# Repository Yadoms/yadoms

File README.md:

<div align="center">

# Yadoms, your home automation solution

**✨ It aims to publish a simple, powerfull, flexible and multiplatforms domotic solution.</a> ✨.**

</div>

<hr>
## Forum

http://www.yadoms.com/forum

## Features

- Edit
- Many devices support
- EnOcean
- ZWave
- RfxCom
- Automation rule
- View customization
- Widgets
- Charts

## Multiplatforms

- Windows
- Linux
- Mac OSX
- Raspberry PI 0,1,2,3,4...
- _probably most of unix based systems_

## Shoutouts

- We thank all the people who contribute, the project exists because of you<br />
- We thank [JetBrains](https://www.jetbrains.com/?from=yadoms) for the licenses<br />

## Licensing

[Refer to LICENSE.md file](LICENSE.md)

## Downloads

[Go to download page](https://github.com/Yadoms/yadoms/releases/)

## Docker

# build the image with the current source code
```bash
docker build -t yadoms .
```

# Run it
```bash
docker run --name yadoms -it -p 8080:8080 yadoms
```

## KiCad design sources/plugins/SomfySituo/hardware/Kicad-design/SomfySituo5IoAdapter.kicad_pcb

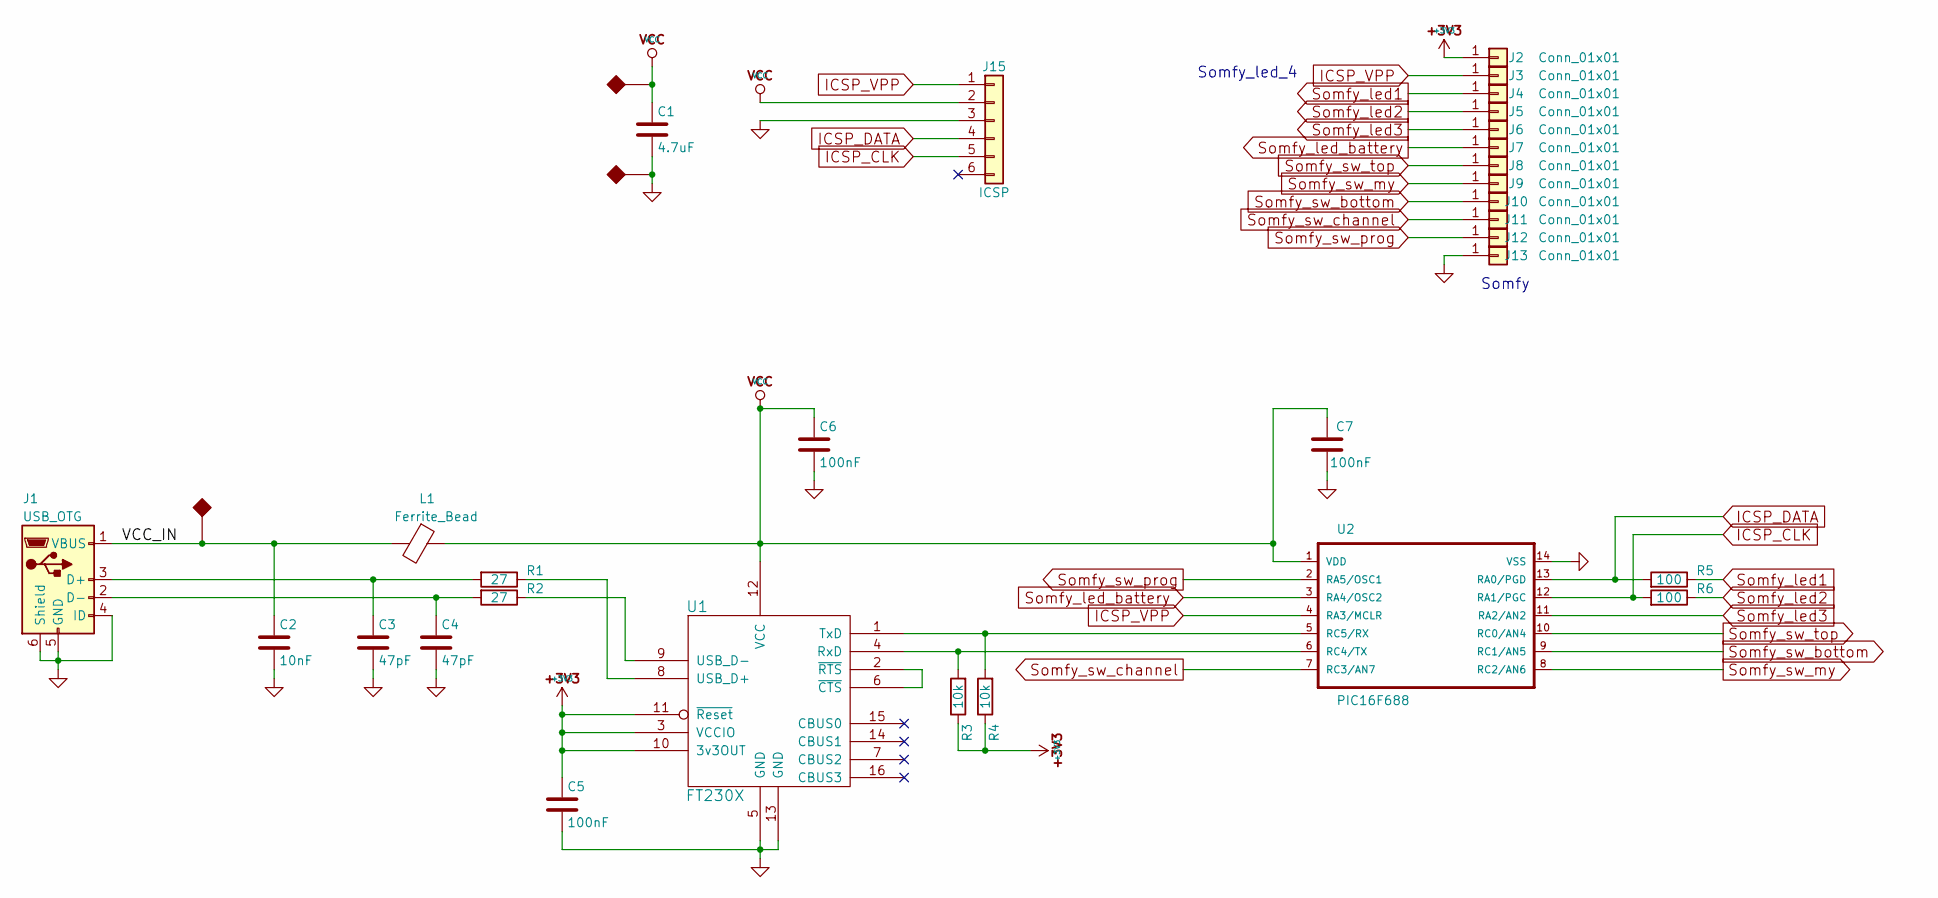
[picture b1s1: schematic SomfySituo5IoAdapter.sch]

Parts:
C1: 4.7uF; C_0805_HandSoldering
C2: 10nF; C_0805_HandSoldering
C3, C4: 47pF; C_0805_HandSoldering
C5, C6, C7: 100nF; C_0805_HandSoldering
J1: USB_OTG; USB_Micro-B_AC0002646
J2, J3, J4, J5, J6, J7, J8, J9, J10, J11, J12, J13: Conn_01x01; Measurement_Point_Square-SMD-Pad_Small
J15: ICSP; AVX_00-9188_006_receiver
L1: Ferrite_Bead; L_0805_HandSoldering
R1, R2: 27; R_0805_HandSoldering
R3, R4: 10k; R_0805_HandSoldering
R5, R6: 100; R_0805_HandSoldering
U1: FT230X; SSOP-16_3.9x4.9mm_Pitch0.635mm
U2: PIC16F688; TSSOP-14_4.4x5mm_Pitch0.65mm

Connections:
+3V3: C5.1, J2.1, R3.1, R4.1, U1.3 (VCCIO), U1.10 (3v3OUT), U1.11 (~Reset)
/VCC_IN: C2.1, J1.1 (VBUS), L1.2
GND: C1.2, C2.2, C3.2, C4.2, C5.2, C6.2, C7.1, J1.4 (ID), J1.5 (GND), J1.6 (Shield), J13.1, J15.3, U1.5 (GND), U1.13 (GND), U2.14 (VSS)
ICSP_CLK: J15.5, R6.2, U2.12 (RA1/PGC)
ICSP_DATA: J15.4, R5.2, U2.13 (RA0/PGD)
ICSP_VPP: J3.1, J15.1, U2.4 (RA3/MCLR)
unnamed: C3.1, J1.3 (D+), R1.2
unnamed: C4.1, J1.2 (D-), R2.2
unnamed: R1.1, U1.8 (USB_D+)
unnamed: R2.1, U1.9 (USB_D-)
unnamed: R3.2, U1.4 (RxD), U2.6 (RC4/TX)
unnamed: R4.2, U1.1 (TxD), U2.5 (RC5/RX)
unnamed: U1.2 (~RTS), U1.6 (~CTS)
Somfy_led1: J4.1, R5.1
Somfy_led2: J5.1, R6.1
Somfy_led3: J6.1, U2.11 (RA2/AN2)
Somfy_led_battery: J7.1, U2.3 (RA4/OSC2)
Somfy_sw_bottom: J10.1, U2.9 (RC1/AN5)
Somfy_sw_channel: J11.1, U2.7 (RC3/AN7)
Somfy_sw_my: J9.1, U2.8 (RC2/AN6)
Somfy_sw_prog: J12.1, U2.2 (RA5/OSC1)
Somfy_sw_top: J8.1, U2.10 (RC0/AN4)
VCC: C1.1, C6.1, C7.2, J15.2, L1.1, U1.12 (VCC), U2.1 (VDD)

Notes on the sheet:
Somfy
Somfy_led_4

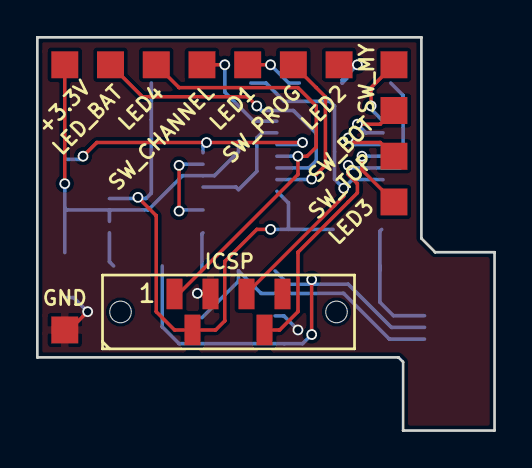
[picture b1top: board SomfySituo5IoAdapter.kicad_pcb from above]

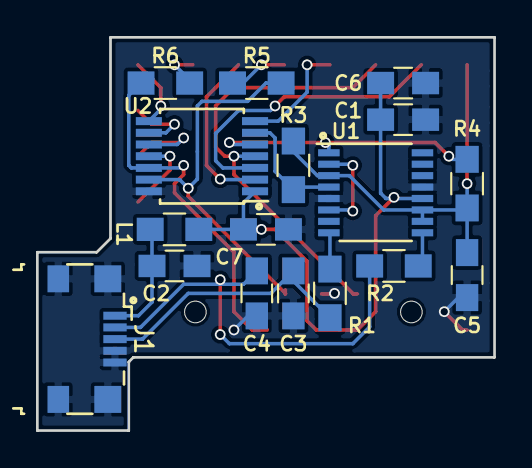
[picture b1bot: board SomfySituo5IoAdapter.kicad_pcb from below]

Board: 2 copper layers, 25.4 x 21.8 mm, 30 parts (17 on the bottom side), 23 nets.

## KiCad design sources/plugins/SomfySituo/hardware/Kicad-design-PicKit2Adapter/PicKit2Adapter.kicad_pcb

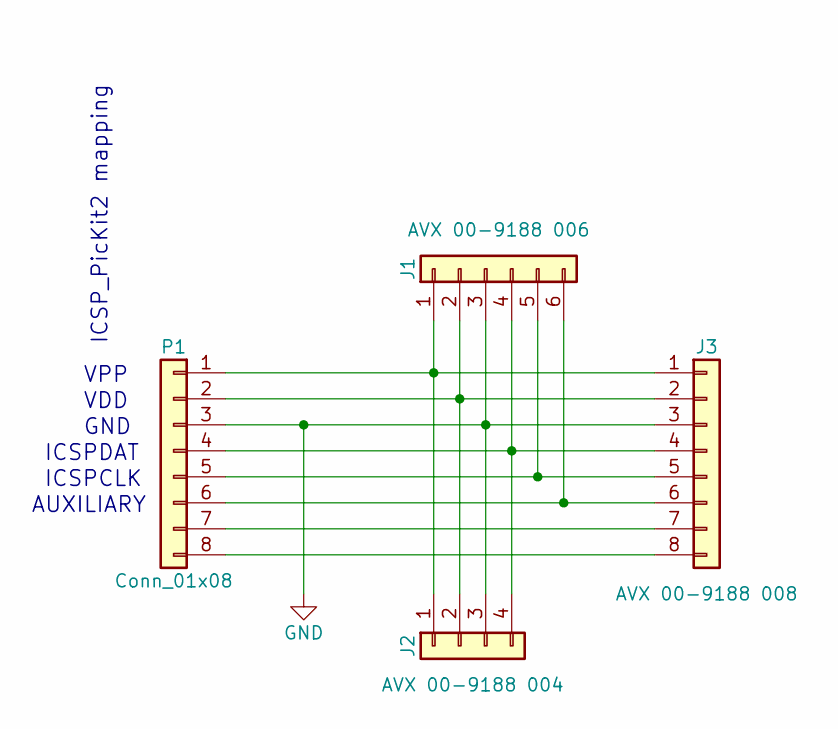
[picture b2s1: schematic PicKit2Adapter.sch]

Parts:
J1: AVX 00-9188 006; AVX_00-9188_006
J2: AVX 00-9188 004; AVX_00-9188_004
J3: AVX 00-9188 008; AVX_00-9188_008
P1: Conn_01x08; Pin_Header_Angled_1x08_Pitch2.54mm

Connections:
GND: J1.3, J2.3, J3.3, P1.3
unnamed: J1.1, J2.1, J3.1, P1.1
unnamed: J1.2, J2.2, J3.2, P1.2
unnamed: J1.4, J2.4, J3.4, P1.4
unnamed: J1.5, J3.5, P1.5
unnamed: J1.6, J3.6, P1.6
unnamed: J3.7, P1.7
unnamed: J3.8, P1.8

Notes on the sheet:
ICSP_PicKit2 mapping
VPP
GND
ICSPDAT
ICSPCLK
AUXILIARY
VDD

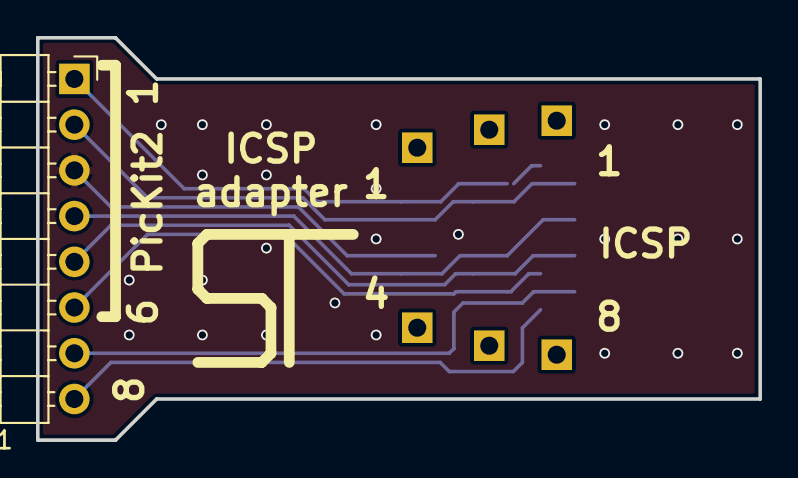
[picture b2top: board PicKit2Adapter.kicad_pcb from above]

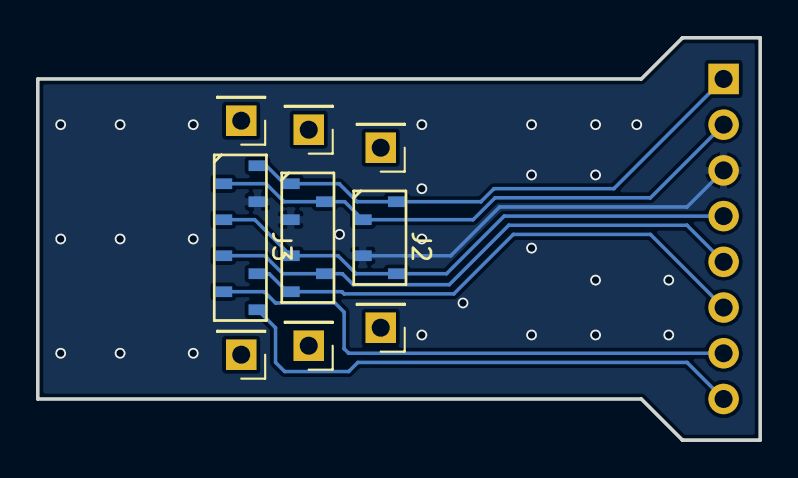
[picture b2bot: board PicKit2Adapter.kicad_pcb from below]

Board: 2 copper layers, 40.1 x 22.4 mm, 4 parts (3 on the bottom side), 8 nets.

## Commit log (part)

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2022-01-07 Refactor updates management
2022-01-10 Fix Yadoms update MD5 check
2022-01-10 Fix Linux build
2022-01-10 Improve 404 management
2022-01-10 Remove TODO
2022-01-10 Add 2 TODOs :-(
2022-01-11 Add updates/forcecheck end-point
2022-01-12 Switch to oatpp v1.3.0 (official release), WIP
2022-01-12 Fix upload
2022-01-13 Manage query params as unordered_multimap
2022-01-13 Add websocket.
    Process IsAlive
2022-01-25 Add new acquisition on websocket management
2022-01-25 Update oatpp
2022-01-25 Revert "Add new acquisition on websocket management"
    This reverts commit 7e2d76df9d03987662bb54e2bf0be462827908ee.
2022-02-03 Manage websocket ping and pong
    Simplify websocket messages format
2022-03-09 Update EnOcean plugin (report some changes from RestApiv2 branch)
2022-03-09 Update build (report some changes from RestApiv2 branch)
2022-03-10 Add D2_04_08 profile support
2022-03-10 Try to fix build
2022-03-10 Add D2_04_XX profiles support
2022-03-11 Update changelog
2022-03-16 Curl v7.82
2022-03-18 Fix curl build
2022-03-28 Add time synchronization message
2022-05-12 Update curlpp options usage
2022-06-05 Update curl (7.83.1)
2022-06-22 Bump Newtonsoft.Json in /ideTools/i18n-check/i18n-check
    Bumps [Newtonsoft.Json](https://github.com/JamesNK/Newtonsoft.Json) from 7.0.1 to 13.0.1.
    - [Release notes](https://github.com/JamesNK/Newtonsoft.Json/releases)
    - [Commits](https://github.com/JamesNK/Newtonsoft.Json/compare/7.0.1...13.0.1)
    ---
    updated-dependencies:
    - dependency-name: Newtonsoft.Json
2022-06-28 Curl 7.84
2022-09-15 Fix websocket closing when shutdown
2022-09-15 Introduce editorconfig file
2022-09-16 Move Poco-specific WS handlers to dedicated folder/namespace
2022-09-16 Add device/keyword creation/deletion WS notifications
2022-09-20 Fix removing unexisting device
2022-09-21 Cleanup (remove CORS handling, only useful for mobile app that would embbed the web client)
2022-09-22 Add GET plugin icon (remove usefulness aliases)
2022-09-22 Add acquisition summary websocket message
2022-09-22 Fix tests
2022-09-23 Add interpreter icon request
2022-09-27 Add HTTPS support
2022-09-27 Speed-up build
2022-09-28 Fix reboot under Linux
2022-09-28 Update changelog
    (cherry picked from commit 9d70c2f2eabac6752474a3c9e9c4166cdc9d2d05)
2022-09-29 Fix can not disable autotest
2022-09-30 Update oatpp-openssl
2022-10-04 Improve MegatecUps (autotest, battery failure detection)
2022-10-05 Disable auto-test if battery declared dead
2022-10-12 Use Curlpp to send emails (Remove Poco)
    Make email subject customizable
2022-10-13 Manage an emails stack in case of connection temporary lost (retry every 2 minutes)
    Supports proxy
2022-10-14 Update MailSender.cpp
    Fix Linux build
2022-10-14 Remove proxy usage (nothing to do with SMTP usage)
2022-10-14 Quick-up cmake
2022-10-17 OATPP is now the default server (on default ports)
2022-10-17 Remove end-point documentation (Swagger)
2022-10-18 Fix mail sender customizable object pattern under Linux
2022-10-19 Add extra-query to reset battery dead flag
2022-10-21 Security patch on configuration
2022-10-21 Use Python3 to run speedtest script
2022-10-21 Update version
2022-10-21 Run speedtest.py script in secure mode
2022-11-15 Enable CORS
2022-11-15 Update /plugins and /plugins-instances parameters and content as camelCase
2022-11-17 Update /system parameters and content as camelCase
2022-11-18 Add pagination in get device REST request (WIP)
2022-11-21 Add pagination on getDevices request
2022-11-28 Update Curlpp
2023-01-03 Fix source file encoding (EnOcean plugin)
2023-01-03 Fix A5-04-xx, A5-09-xx and D2-02-xx devices pairing
2023-01-04 Release EnOcean plugin v2.1.2
2023-02-22 2.5.3
2023-02-26 Add pagination on GET Plugin instances EP
2023-02-26 Add pagination on GET Available Plugin EP
2023-02-28 Fix VS2022 build
2023-02-28 Manage plugins locales (WIP)
2023-03-01 Fix test
2023-03-01 Manage locales (for plugins and interpreters)
2023-03-18 Fix all plugins package.in.json files
2023-03-18 Fix ZWave package.in.json
2023-03-19 Add /system/binding EP
2023-03-22 Filter system plugin for GET /plugins-instances EP
2023-04-03 Populate "__Binding__" fields server-side in available plugins request (WIP)
2023-04-03 Fix containers merge Apply filter to USB devices
2023-04-04 Manage all binding data from plugins
2023-04-04 Manage locale for available plugins request (name, description and configuration schema)
2023-04-05 Fix locales condition
2023-04-05 Fix crash when some plugin has no conf schema
2023-04-05 Improve robustness
2023-04-12 Update SMSDialer descriptions (use markdown for URLs)
2023-04-12 Fix some plugin configurations containing checkbox
2023-04-12 Fix step/precision confusion
2023-04-12 Fix typo
2023-04-14 Use checkboxSection in plugin configurations
2023-04-14 Use time type in configuration
2023-04-15 Add StringExtension::replaceValues
2023-04-16 Use multiselectSection for rfplayer and rfxcom
2023-04-27 Plugin full state
2023-04-29 Fix unit tests
2023-04-29 Fix DataContainer regression
2023-05-15 Manage plugin full states
2023-05-16 Fix unit test
2023-05-16 multiselectSection to multiSelectSection
2023-05-16 Add placeholder and nothingFound in multiselect
2023-05-30 Remove activeSectionText usages.
    Add empty content in Linky package.json
2023-09-20 Add log at REST answer
2023-09-20 Add log on internal server error
2023-09-20 Log exception at available plugin get method
2023-09-20 Remove log
2023-09-20 Fix Linux on OneWire plugin
2023-09-21 add yadoms Dockerfile
2023-09-22 Fix available plugins list build when a plugin is malformed
2023-09-22 Update some dependancies
2023-10-04 SSE (crash at stop)
2023-10-04 Fix SSE crash
2023-10-04 Add connections counter
2023-10-04 Create a SSE connection class (WIP)
2023-10-05 Refactor connection handler
2023-10-06 Send acquisitions in SSE mode
2023-10-11 Handle SSE connection closing
2023-10-12 Finalize SSE POC
2023-10-25 Fix typo in Blockly implementation
2023-11-07 Fix error managment on websocket
2023-11-07 Update dependencies
2023-11-08 Upload logs
2023-11-08 Try to fix cross-compile for Raspberry Pi
2023-11-08 [GH] Generalize upload CMake logs on build failure
2023-11-14 Remove MacOSx support (finally ! :-D )
2023-11-15 Use Oatpp official
2023-12-04 Add type for each item of multiSelectSection
2023-12-05 Fix websocket close
2023-12-05 Log all keywords change
2024-05-31 fix rfxcom package.in.json
2024-05-31 Add Plugin configuration merger (WIP)
2024-05-31 Fix build
2024-06-02 Apply "configurationWithSchema" for CREATE and UPDATE (if "configurationWithSchema" provided instead on "configuration", configuration will be extracted before to be saved in database. If "configurat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
2024-06-03 Add all types (all sections types, time...) in PluginConfigurationMerger
2024-06-03 Fix configuration merger at first start (with no configuration)
2024-06-04 Fix Accept-Language header processing (and add quality flag management)
2024-06-05 Set values to default in merged configuration
2024-06-05 Fix binded enum default value
2024-06-06 Remove invisible fields from PluginConfigurationMerger
2024-06-07 Fix activeSection for radio and combo sections
2024-06-19 [Mailsender plugin] Manage new radioSection format
2024-06-24 Add Rain 9 support (TFA 30.3233 rain sensor)
2024-06-24 Update rfxcom version
2024-06-26 [RFXCom] Make version official
2024-06-26 Update MailSender changelog
2024-06-26 [RfPlayer plugin] Manage new radioSection format
2024-06-26 [fakePlugin plugin] Manage new radioSection format
2024-06-26 Update build
2024-06-26 Update yadomsVersion extract regarding https://github.blog/changelog/2022-10-11-github-actions-deprecating-save-state-and-set-output-commands/
2024-06-27 Try to fix Github Actions warnings
2024-08-21 Update Cotire
2024-08-21 Fix some CMake warnings
2024-08-21 Improve GET PluginsInstances internal server error (500) message
2024-08-26 Try to fix OpenZWave build
2024-08-26 Try to fix Windows build
2024-08-30 Update Windows build action
2024-08-30 Add platform to dockerfile
2024-08-30 Revert "Update Windows build action"
    This reverts commit 276d8dfc98913de9ef296182c812281594c6dee8.
2024-09-03 Fix startup
2024-09-03 Bump actions/download-artifact from 2 to 4.1.7 in /.github/workflows
    Bumps [actions/download-artifact](https://github.com/actions/download-artifact) from 2 to 4.1.7.
    - [Release notes](https://github.com/actions/download-artifact/releases)
    - [Commits](https://github.com/actions/download-artifact/compare/v2...v4.1.7)
    ---
    updated-dependencies:
    - dependency-name: actions/download-artifact
2024-09-05 Fix plugins custom messages handling
2024-09-05 Refactor plugin config/schema merge
2024-09-05 Accept configuration or configuration with schema when create/update plugin instance
2024-09-09 Update curl
2024-09-10 update docker commands
2024-09-10 update dockerfile with multi stage
2024-09-16 Fix LametricTime crash when reinit configuration for manually pairing
2024-09-16 GHA : update actions/upload-artifact to v4.4.0
2024-09-16 Fix LametricTime crash when reinit configuration for manually pairing
    (cherry picked from commit 5f3ed1a8f176da788ba6dd10eadd8836557667d8)
2025-01-07 Try to fix GH build
2025-01-07 Try to fix build
    # Conflicts:
    # sources/shared/shared/compression/Extract.cpp
2025-01-08 Revert "Try to fix build"
    This reverts commit 532c6684ead15e0c6e551d65c99804023be62771.
2025-01-08 Revert "Try to fix build"
    This reverts commit 5f9b3ed1dcee9bd576dc918ac0f96f353767ca92.
2025-01-08 Try to fix tests
2025-01-11 Trace test suite
2025-01-14 Try to fix build
    (cherry picked from commit 393e965ca69ee2514887a337a924a5d634cc1921)
2025-01-14 Use official curlpp
2025-01-31 EnOcean : update manufacturers
2025-01-31 EnOcean : update version
2025-08-05 EnOcean - Fix read data for A5-10-xx, A5-11-xx, D2-04-xx, F6-04-xx and F6-10-xx profiles
2025-08-07 EnOcean 2.1.4
2025-08-12 Set battery low level to 10%
    Make summer mode and set point inverse to read/write
2025-08-13 Add some init functions
2025-08-19 Try to build with C++17
2025-08-25 Enable LearnMode if supported by dongle
2025-08-26 Refactor messages
2025-08-27 Update CMakeLists files
2025-08-27 Add logs
2025-09-02 Pair 4BS bidirectionnal devices
2025-09-09 Implement sendCommand on request
2025-09-09 Send command to A5-20-01 (WIP)
2025-09-12 Fix teachin
    Fix A5_20_01 answer
2025-09-14 Fix A5-20-01
2025-09-14 Remove pairing auto mode
2025-09-14 Refactor pairing
2025-10-10 Device configuration (WIP)
2025-10-14 Retrieving device configuration (WIP)
2025-10-15 C++17, Boost 1.89, RPi2 cross-compile, Remove Pyhon2.7 script interpreter
2025-10-15 CMake message
2025-10-15 Fix Windows build
2025-10-16 Get static configurable device
2025-10-17 Get device static configuration (with values and labels)
2025-10-17 Dynamic device configuration support (WIP)
2025-10-19 Dynamic device configuration support (finished)
2025-10-19 Fix TODO
2025-10-22 Finish device rest service
2025-11-12 Fix driving A5_20_01 device
2025-11-12 Fix log
2025-11-21 [EnOcean] Fixes on A5-20-01 profile
2025-12-10 Update Windows CMake
2025-12-11 Cross-compilation for RaspberryPi
2025-12-15 Fix A5-20-01 initial command
2025-12-16 Add A5-20-06 profile support
2026-01-01 Fix "Actuator Set Output" command on D2-01-0E profile
2026-01-01 Fix temperature conversion
2026-01-02 Fix A5-20-06
2026-01-09 Build (WIP)
2026-01-09 Fix build (WIP)
2026-01-11 [StreamDeck] Update hidapi
2026-01-15 Update GH-actions
2026-01-21 unit test workflow
2026-01-21 Fix curlpp
2026-01-21 set CMAKE_POSITION_INDEPENDENT_CODE
2026-01-27 Update SQLite
2026-01-28 Fix protobuf lib name
2026-01-30 Try build with protobuf
2026-01-30 Revert
2026-01-30 Remove Poco integer types
2026-02-02 Fix options
2026-02-02 Logs
2026-02-02 Remove not needed dependency
2026-02-04 Update test build script for Windows
2026-02-04 Unit tests
2026-02-05 Suspend Windows build and rpi images generation
2026-02-09 Try to fix unit tests
2026-03-12 Fix crash when closing websocket
2026-03-20 Add widgets endpoint (WIP)
    Add Bruno collection to test end-points
2026-03-23 Add APIv1 Bruno collection to test end-points
2026-03-23 Add WS v2 Bruno collection
2026-03-25 Prepare db migration
2026-04-24 Fix acquisitions API

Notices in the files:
README.md:
GPLv3 License
